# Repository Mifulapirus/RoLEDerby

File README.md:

# README #

RoLEDerby project by HirikiLabs

### What is this repository for? ###

* Electronics and software to light-up Roller derby matches
* V 0.1

### Set Up ###

* Build the electronics

### Contact ###
* @hirikilabs
* @mifulapirus

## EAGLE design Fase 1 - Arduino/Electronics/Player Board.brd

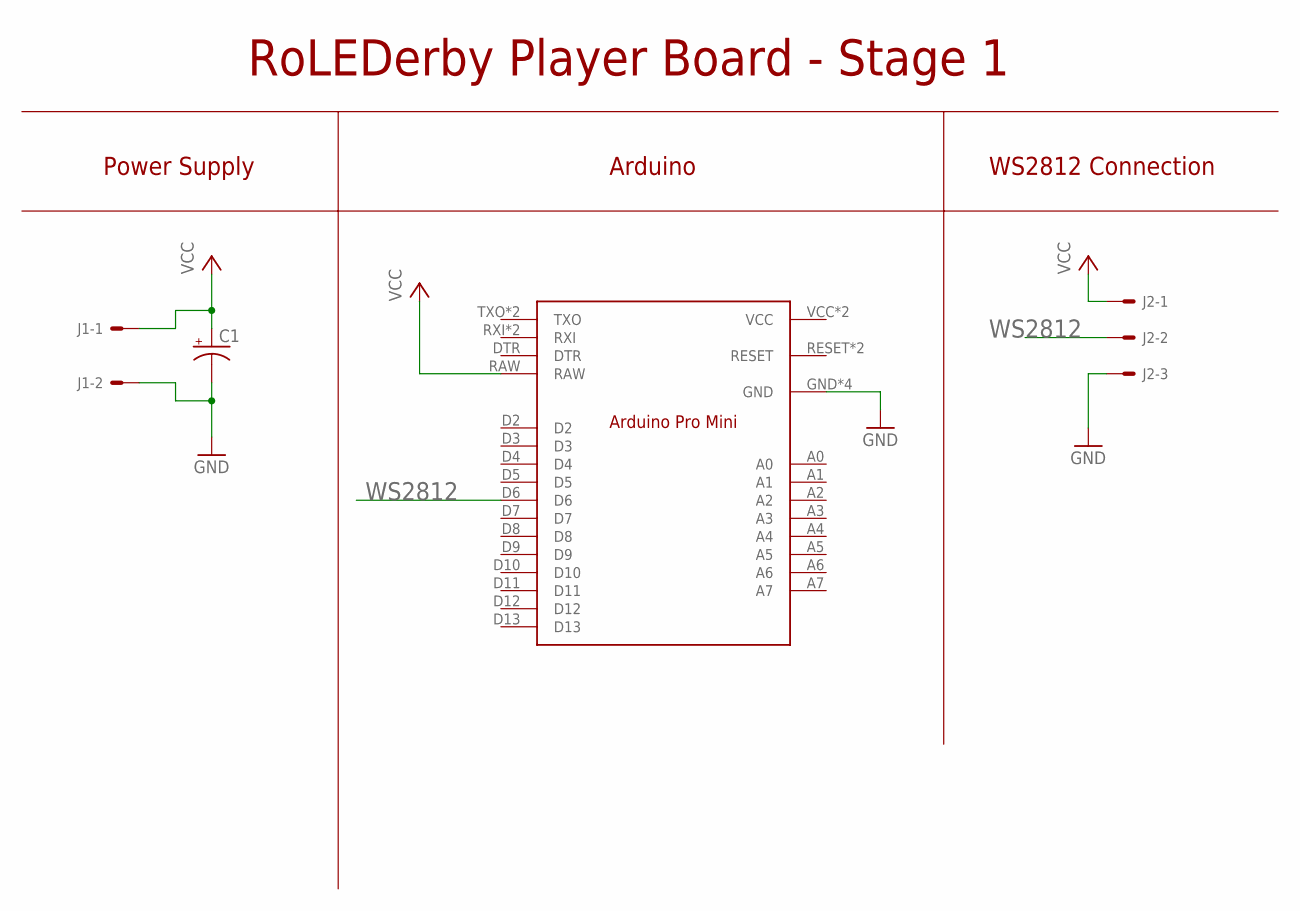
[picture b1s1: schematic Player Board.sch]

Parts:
C1: CAP_POLPTH2; CPOL-RADIAL-10UF-25V
J1: 22-27-2021-02; 6410-02
J2: 22-27-2031-03; 6410-03
U$1: ARDUINO_PRO_MINI

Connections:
GND: C1.2 (-), J1.2, J2.3, U$1.GND, U$1.GND1 (GND), U$1.GND2 (GND), U$1.GND3 (GND)
VCC: C1.1 (+), J1.1, J2.1, U$1.RAW
WS2812: J2.2, U$1.D6

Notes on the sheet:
RoLEDerby Player Board - Stage 1
Power Supply
Arduino
WS2812 Connection

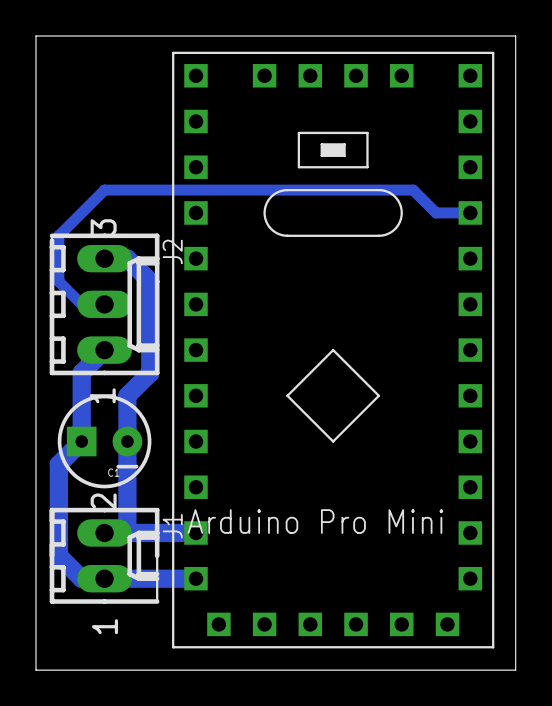
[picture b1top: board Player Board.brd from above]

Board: 2 copper layers, 26.6 x 35.2 mm, 4 parts (0 on the bottom side), 3 nets.

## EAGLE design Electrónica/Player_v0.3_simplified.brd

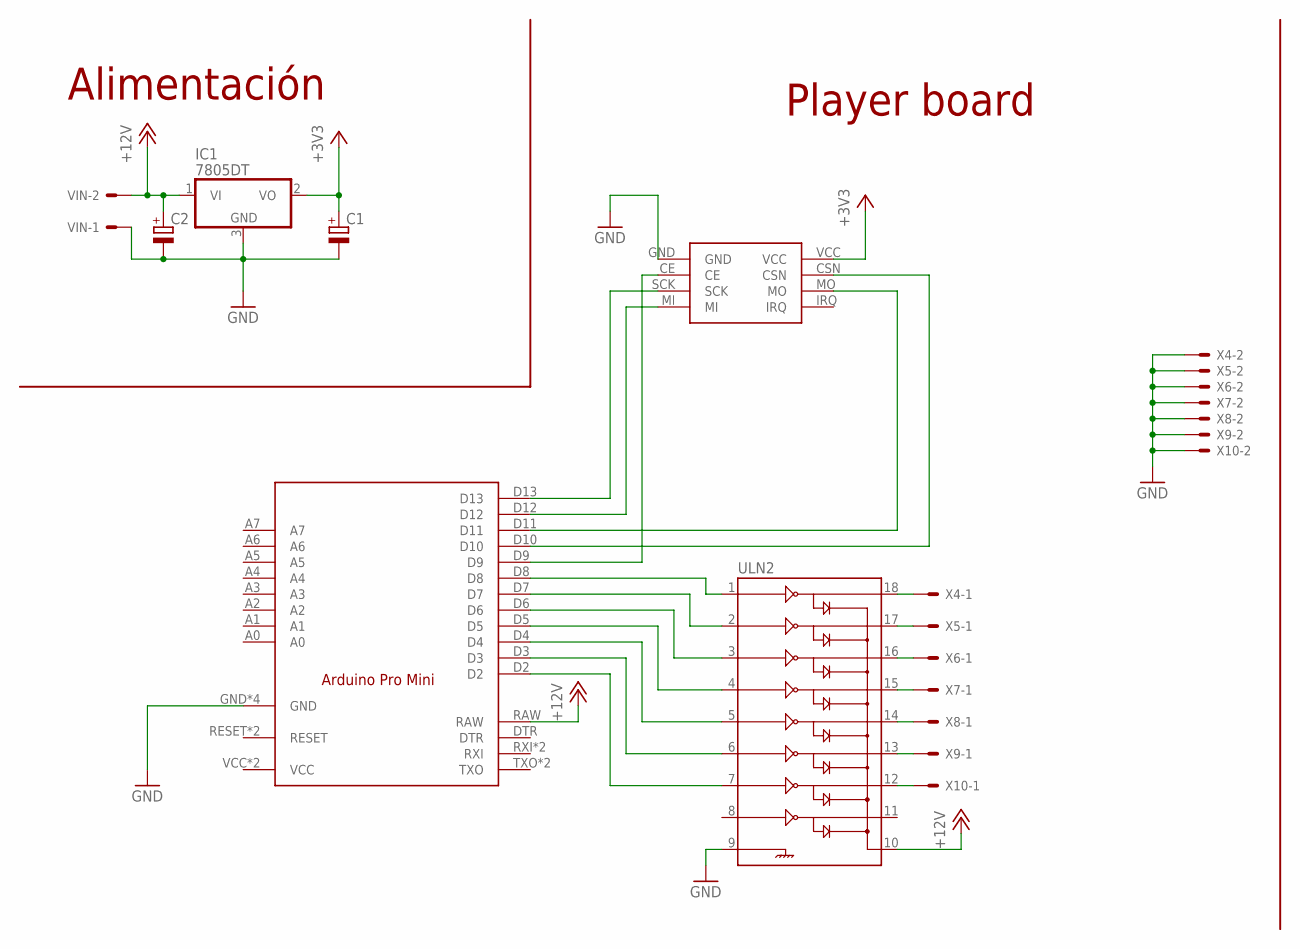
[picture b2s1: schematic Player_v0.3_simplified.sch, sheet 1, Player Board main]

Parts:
C1, C2: CPOL-EUE2.5-5; E2,5-5
IC1: 7805DT; TO252
U$1: ARDUINO_PRO_MINI
U$5: NRF24L01_8PIN
ULN2: ULN2803SOIC; SO018
VIN: KK-156-2
X4, X5, X6, X7, X8, X9, X10: KK-156-2

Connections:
+3V3: C1.+, IC1.2 (VO), U$5.VCC; also elsewhere on the board
+12V: C2.+, IC1.1 (VI), U$1.RAW, ULN2.10, VIN.2; also elsewhere on the board
GND: C1.-, C2.-, U$1.GND, U$1.GND1 (GND), U$1.GND2 (GND), U$1.GND3 (GND), U$5.GND, ULN2.9, VIN.1, X4.2, X5.2, X6.2, X7.2, X8.2, X9.2, X10.2; also elsewhere on the board
unnamed: U$1.D7, ULN2.2
unnamed: U$1.D3, ULN2.6
unnamed: U$1.D5, ULN2.4
unnamed: U$1.D6, ULN2.3
unnamed: ULN2.18, X4.1
unnamed: ULN2.17, X5.1
unnamed: ULN2.16, X6.1
unnamed: ULN2.15, X7.1
unnamed: U$1.D12, U$5.MI
unnamed: U$1.D11, U$5.MO
unnamed: U$1.D13, U$5.SCK
unnamed: U$1.D10, U$5.CSN
unnamed: ULN2.14, X8.1
unnamed: ULN2.13, X9.1
unnamed: ULN2.12, X10.1
unnamed: U$1.D9, U$5.CE
unnamed: U$1.D2, ULN2.7
unnamed: U$1.D8, ULN2.1
unnamed: U$1.D4, ULN2.5

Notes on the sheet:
Alimentación
Player board

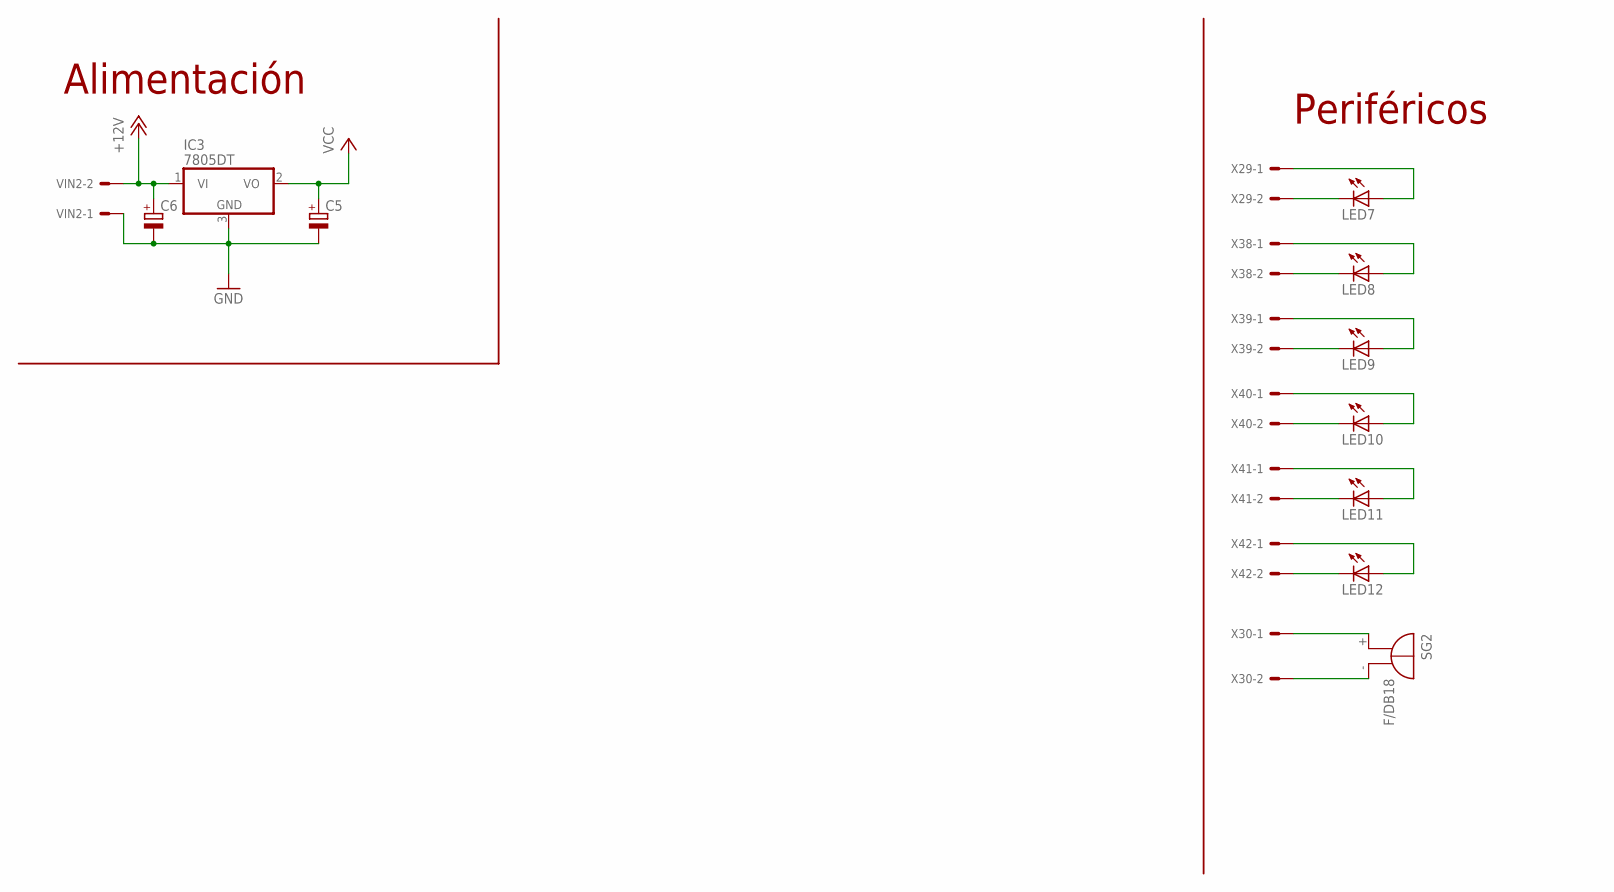
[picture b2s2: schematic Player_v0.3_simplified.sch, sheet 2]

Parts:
C5, C6: CPOL-EUE2.5-5; E2,5-5
IC3: 7805DT; TO252
LED7, LED8, LED9, LED10, LED11, LED12: LED5MM
SG2: F/DB18
VIN2: KK-156-2
X29, X30, X38, X39, X40, X41, X42: KK-156-2

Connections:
+12V: C6.+, IC3.1 (VI), VIN2.2; also elsewhere on the board
GND: C5.-, C6.-, VIN2.1; also elsewhere on the board
unnamed: LED7.A, X29.1
unnamed: LED7.K (C), X29.2
unnamed: LED8.A, X38.1
unnamed: LED8.K (C), X38.2
unnamed: LED9.A, X39.1
unnamed: LED9.K (C), X39.2
unnamed: LED10.A, X40.1
unnamed: LED10.K (C), X40.2
unnamed: LED11.A, X41.1
unnamed: LED11.K (C), X41.2
unnamed: LED12.A, X42.1
unnamed: LED12.K (C), X42.2
unnamed: SG2.+, X30.1
unnamed: SG2.-, X30.2
VCC: C5.+, IC3.2 (VO); also elsewhere on the board

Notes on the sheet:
Alimentación
Periféricos

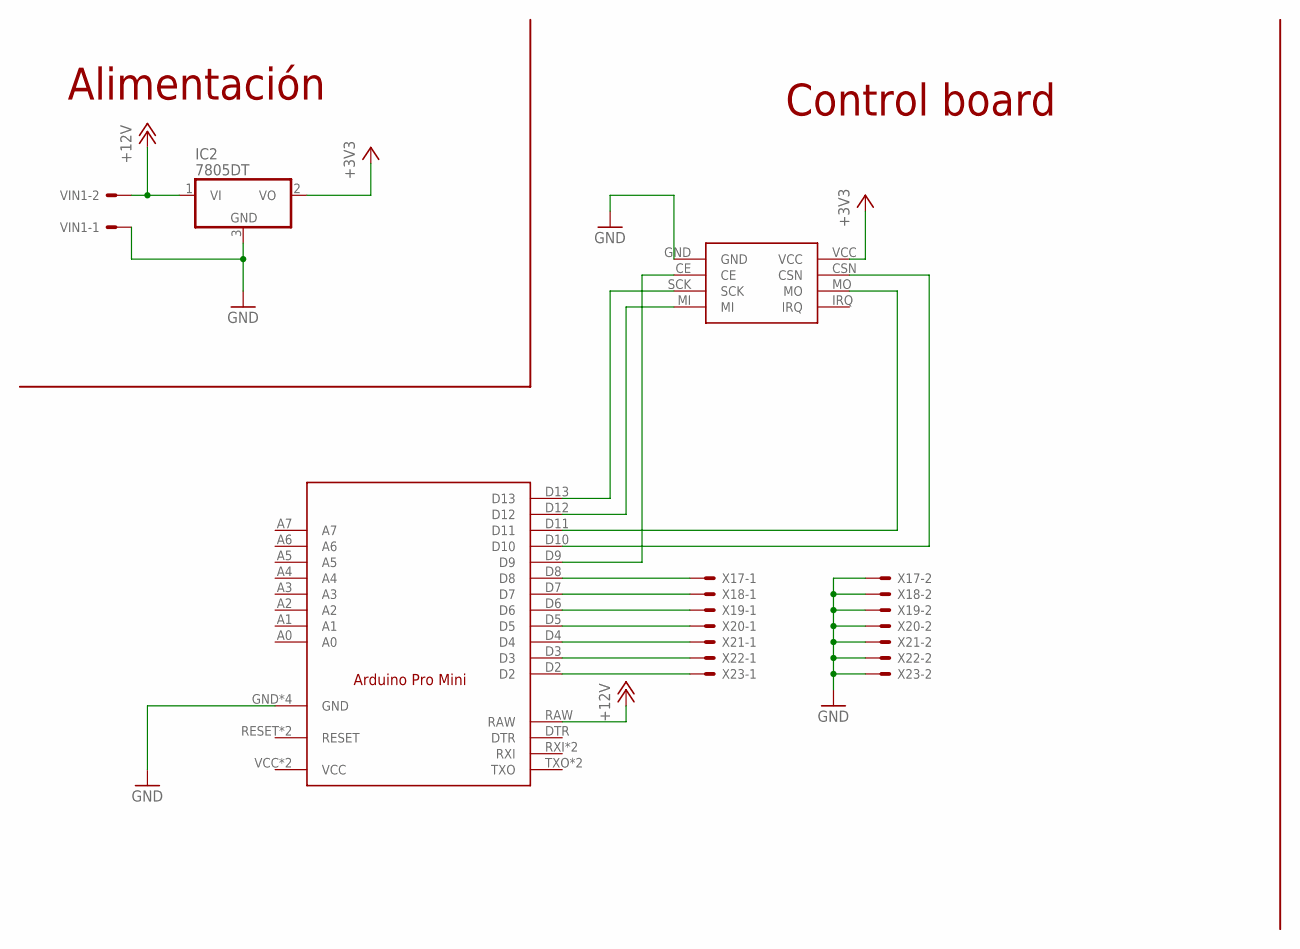
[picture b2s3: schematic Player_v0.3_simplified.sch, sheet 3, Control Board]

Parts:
IC2: 7805DT; TO252
U$2: NRF24L01_8PIN
U$3: ARDUINO_PRO_MINI
VIN1: KK-156-2
X17, X18, X19, X20, X21, X22, X23: KK-156-2

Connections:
+3V3: IC2.2 (VO), U$2.VCC; also elsewhere on the board
+12V: IC2.1 (VI), U$3.RAW, VIN1.2; also elsewhere on the board
GND: U$2.GND, U$3.GND, U$3.GND1 (GND), U$3.GND2 (GND), U$3.GND3 (GND), VIN1.1, X17.2, X18.2, X19.2, X20.2, X21.2, X22.2, X23.2; also elsewhere on the board
unnamed: U$2.MI, U$3.D12
unnamed: U$2.MO, U$3.D11
unnamed: U$2.SCK, U$3.D13
unnamed: U$2.CSN, U$3.D10
unnamed: U$3.D5, X20.1
unnamed: U$3.D6, X19.1
unnamed: U$3.D8, X17.1
unnamed: U$3.D3, X22.1
unnamed: U$3.D4, X21.1
unnamed: U$3.D7, X18.1
unnamed: U$3.D2, X23.1

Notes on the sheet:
Alimentación
Control board

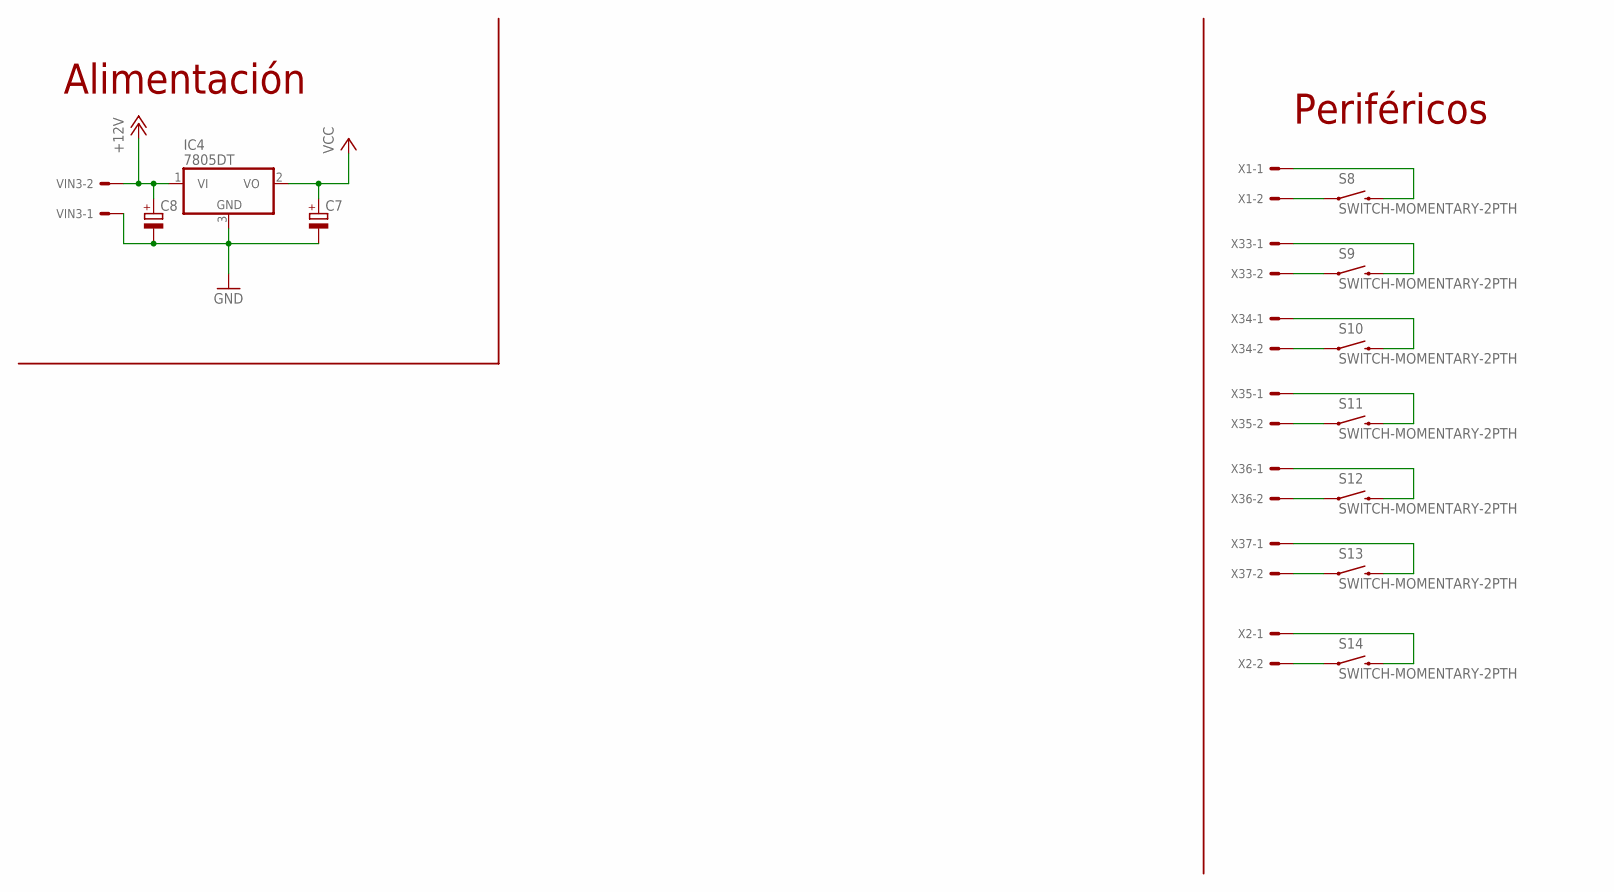
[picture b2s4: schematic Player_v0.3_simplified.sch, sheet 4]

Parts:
C7, C8: CPOL-EUE2.5-5; E2,5-5
IC4: 7805DT; TO252
S8, S9, S10, S11, S12, S13, S14: SWITCH-MOMENTARY-2PTH; TACTILE-PTH
VIN3: KK-156-2
X1, X2, X33, X34, X35, X36, X37: KK-156-2

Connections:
+12V: C8.+, IC4.1 (VI), VIN3.2; also elsewhere on the board
GND: C7.-, C8.-, VIN3.1; also elsewhere on the board
unnamed: S8.3 (2), X1.1
unnamed: S9.3 (2), X33.1
unnamed: S10.3 (2), X34.1
unnamed: S11.3 (2), X35.1
unnamed: S12.3 (2), X36.1
unnamed: S13.3 (2), X37.1
unnamed: S14.3 (2), X2.1
unnamed: S14.1, X2.2
unnamed: S13.1, X37.2
unnamed: S12.1, X36.2
unnamed: S11.1, X35.2
unnamed: S10.1, X34.2
unnamed: S9.1, X33.2
unnamed: S8.1, X1.2
VCC: C7.+, IC4.2 (VO); also elsewhere on the board

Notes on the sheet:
Alimentación
Periféricos

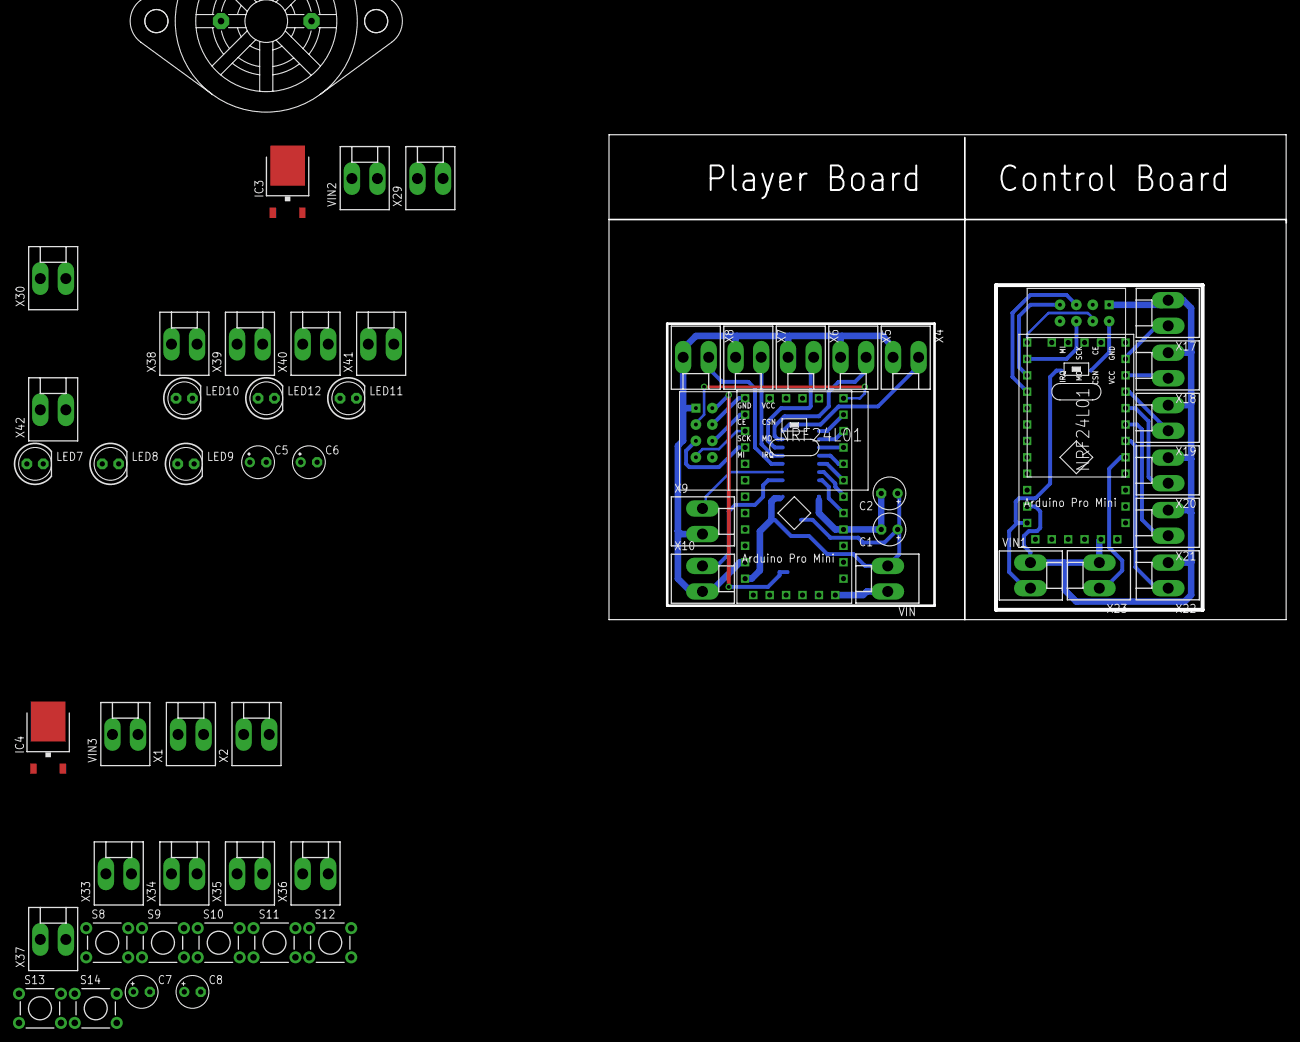
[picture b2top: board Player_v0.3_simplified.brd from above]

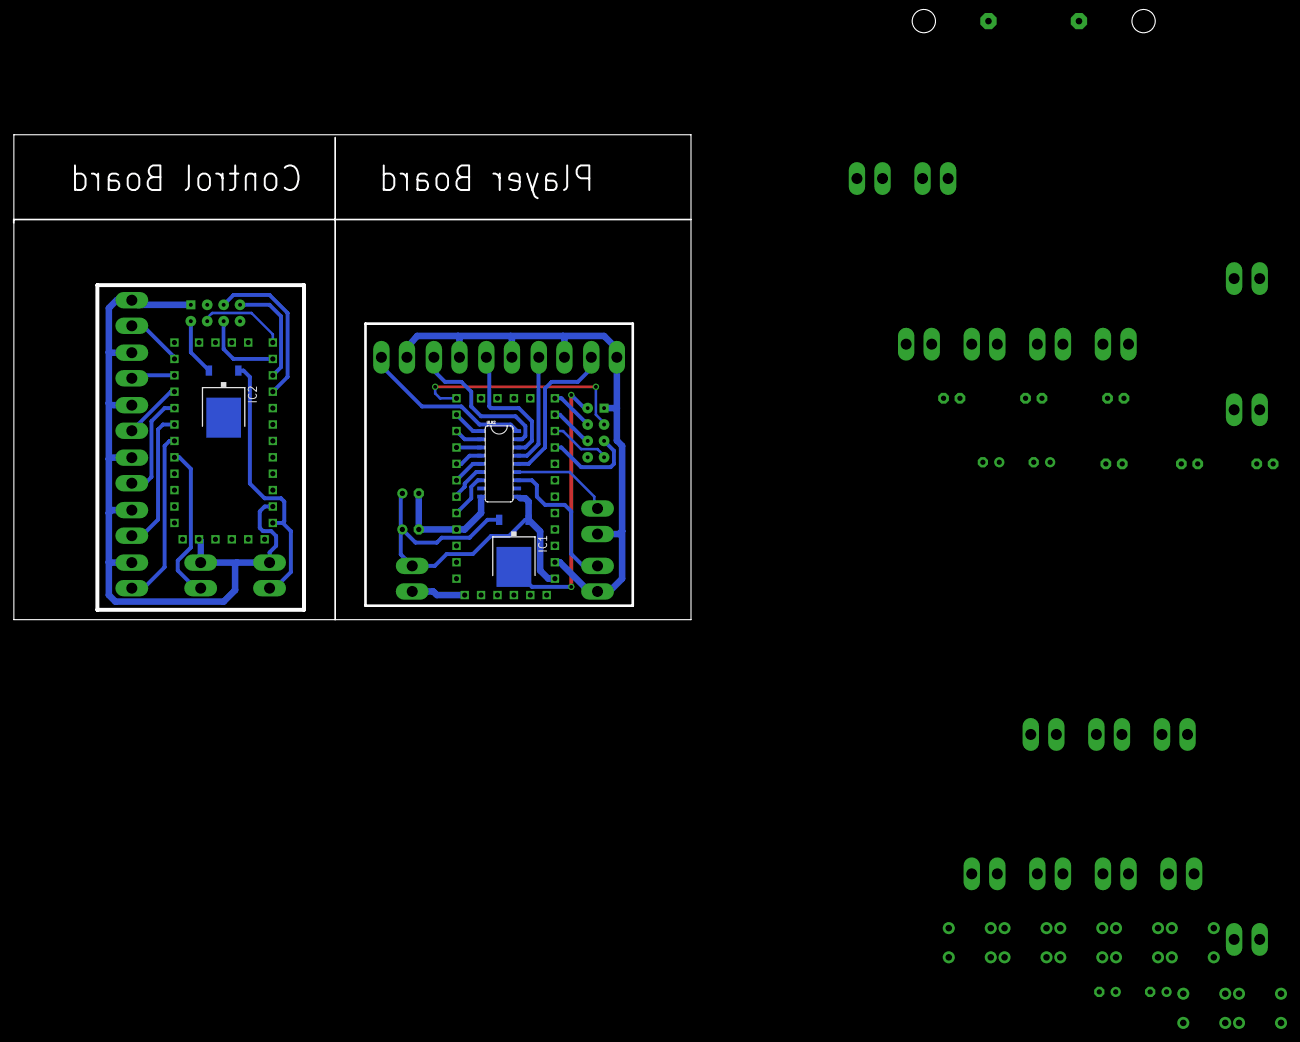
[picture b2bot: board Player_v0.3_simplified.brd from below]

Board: 2 copper layers, 104.9 x 75.1 mm, 61 parts (3 on the bottom side), 62 nets.

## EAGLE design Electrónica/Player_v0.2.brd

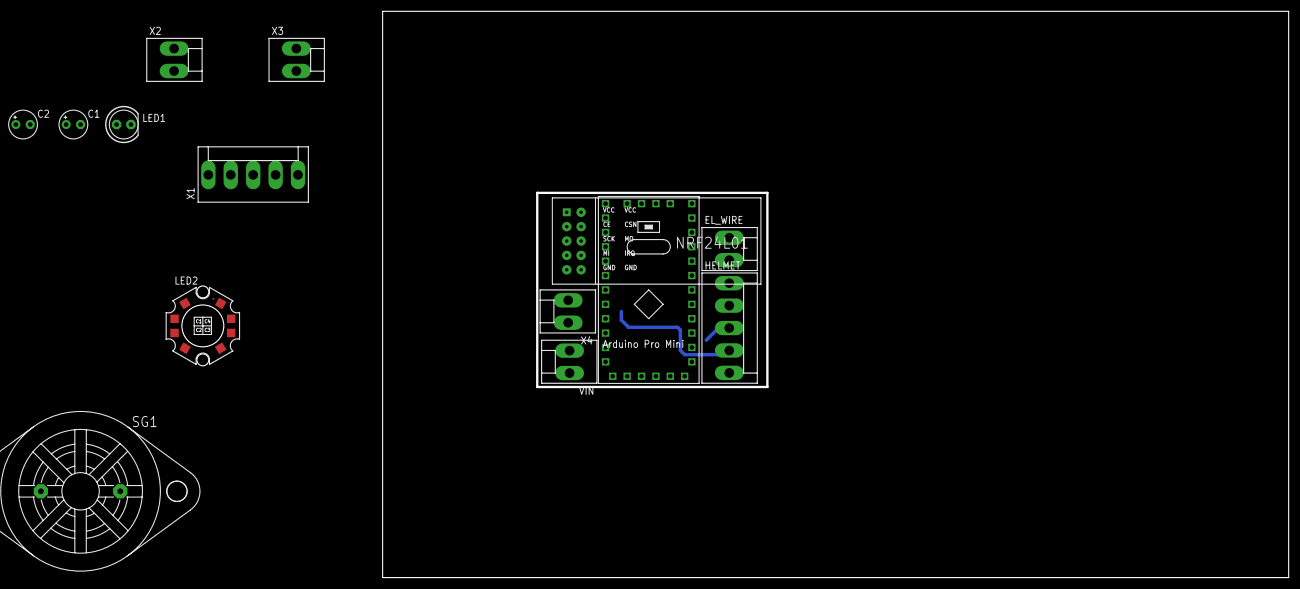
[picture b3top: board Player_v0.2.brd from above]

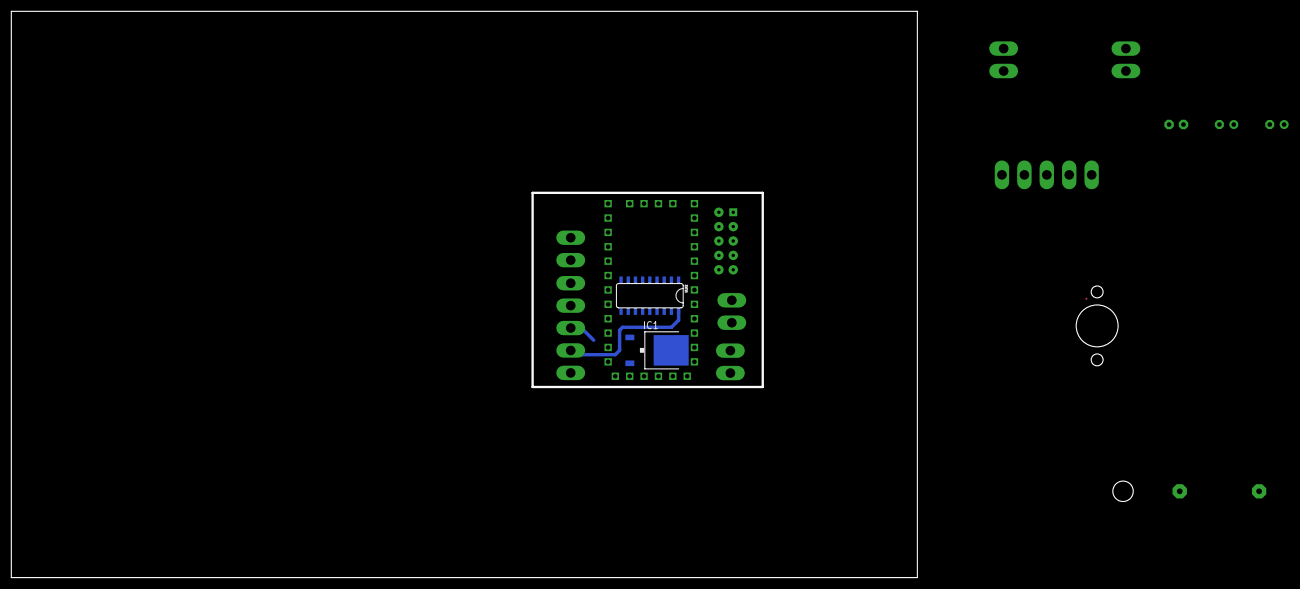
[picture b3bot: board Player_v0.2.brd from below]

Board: 2 copper layers, 195.4 x 100.0 mm, 16 parts (2 on the bottom side), 28 nets.

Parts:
C1, C2: E2,5-5
EL_WIRE: KK-156-2
HELMET: KK-156-5
IC1: 7805DT; TO252
LED1: LED5MM
LED2: ACULEDVHL-RGBY; ACULEDVHL
SG1: F/DB18
U$1: ARDUINO_PRO_MINI
U$2: NRF24L01; NRF24L01-DEALEXTREME
ULN2: SO018
VIN: KK-156-2
X1: KK-156-5
X2, X3, X4: KK-156-2

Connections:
+12V: C2.+, EL_WIRE.1, HELMET.5, IC1.1, ULN2.10, VIN.2, X4.1
GND: C1.-, C2.-, U$1.GND, U$1.GND1, U$1.GND2, U$1.GND3, U$2.GND, U$2.GND_1, ULN2.9, VIN.1
unnamed: U$1.D8, ULN2.2
unnamed: U$1.D4, ULN2.6
unnamed: U$1.D6, ULN2.4
unnamed: U$1.D7, ULN2.3
unnamed: LED2.8, X1.4
unnamed: LED2.6, X1.3
unnamed: LED2.4, X1.2
unnamed: LED2.2, X1.1
unnamed: U$1.D12, U$2.MI
unnamed: U$1.D11, U$2.MO
unnamed: U$1.D13, U$2.SCK
unnamed: U$1.D10, U$2.CSN
unnamed: HELMET.4, ULN2.18
unnamed: HELMET.3, ULN2.17
unnamed: HELMET.2, ULN2.16
unnamed: HELMET.1, ULN2.15
unnamed: EL_WIRE.2, ULN2.14
unnamed: SG1.+, X3.2
unnamed: SG1.-, X3.1
unnamed: ULN2.13, X4.2
unnamed: LED1.K, X2.1
unnamed: LED1.A, X2.2
unnamed: U$1.D9, ULN2.1
unnamed: LED2.1, LED2.3, LED2.5, LED2.7, X1.5
unnamed: U$1.D5, ULN2.5
VCC: C1.+, IC1.2, U$1.VCC, U$1.VCC1, U$2.CE, U$2.VCC, U$2.VCC_1

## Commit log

2015-04-05 - Simplified version divided into Player board, control board and peripherals
2015-04-05 - Created the folder tree and some pictures
2015-04-05 - unified Peripherals and boards
2015-04-22 - Deprecated old Radio controlled version
2015-04-22 Created Stage 1 folder initial firmware version by Jesus
2015-04-22 Electronics first version

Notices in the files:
parts and their libraries:
SparkFun-PowerIC: Licensing: Creative Commons ShareAlike 4.0 International - https://creativecommons.org/licenses/by-sa/4.0
